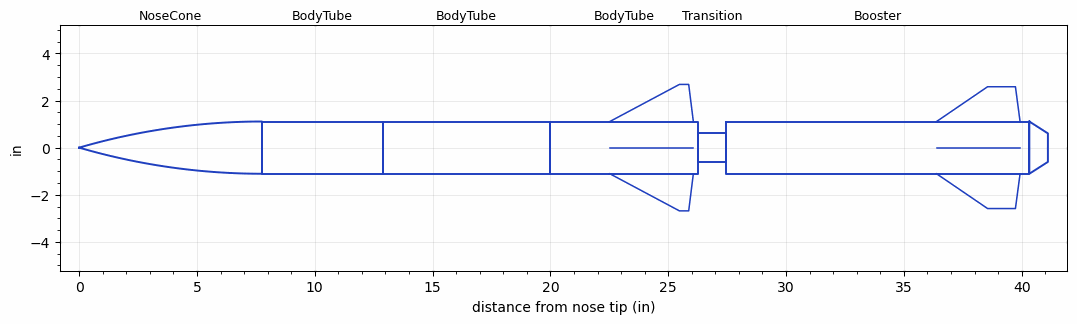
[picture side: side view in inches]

<RASAeroDocument>
 <FileVersion>2</FileVersion>
 <RocketDesign>
  <NoseCone>
   <Length>7.7579</Length>
   <Diameter>2.217</Diameter>
   <Shape>Tangent Ogive</Shape>
   <Location>0</Location>
  </NoseCone>
  <BodyTube>
   <Length>5.1181</Length>
   <Diameter>2.217</Diameter>
   <Location>7.7579</Location>
  </BodyTube>
  <BodyTube>
   <Length>7.0866</Length>
   <Diameter>2.217</Diameter>
   <Location>12.876</Location>
  </BodyTube>
  <BodyTube>
   <Length>6.2992</Length>
   <Diameter>2.217</Diameter>
   <Location>19.9626</Location>
   <Fin>
    <Count>4</Count>
    <Chord>3.5433</Chord>
    <Span>1.5748</Span>
    <SweepDistance>2.9527</SweepDistance>
    <TipChord>0.3937</TipChord>
    <Thickness>0.1181</Thickness>
    <Location>3.7401</Location>
    <AirfoilSection>Subsonic NACA</AirfoilSection>
   </Fin>
  </BodyTube>
  <Transition>
   <Length>1.1811</Length>
   <Diameter>1.2087</Diameter>
   <RearDiameter>1.2087</RearDiameter>
   <Location>26.2618</Location>
  </Transition>
  <Booster>
   <Length>12.8819</Length>
   <Diameter>2.217</Diameter>
   <RailGuideDiameter>0.3725</RailGuideDiameter>
   <RailGuideHeight>0.305</RailGuideHeight>
   <Location>27.4429</Location>
   <BoattailLength>0.7874</BoattailLength>
   <BoattailRearDiameter>1.2087</BoattailRearDiameter>
   <Fin>
    <Count>4</Count>
    <Chord>3.5433</Chord>
    <Span>1.4764</Span>
    <SweepDistance>2.1653</SweepDistance>
    <TipChord>1.1811</TipChord>
    <Thickness>0.1181</Thickness>
    <Location>3.937</Location>
    <AirfoilSection>Subsonic NACA</AirfoilSection>
   </Fin>
  </Booster>
  <Surface>Rough Camouflage Paint</Surface>
  <CD>0</CD>
  <ModifiedBarrowman>False</ModifiedBarrowman>
  <Turbulence>False</Turbulence>
  <UseBooster1>True</UseBooster1>
  <UseBooster2>False</UseBooster2>
 </RocketDesign>
 <LaunchSite>
  <Altitude>0</Altitude>
  <Pressure>29.9214</Pressure>
  <RodAngle>0</RodAngle>
  <RodLength>39.37</RodLength>
  <Temperature>59</Temperature>
  <WindSpeed>4.4739</WindSpeed>
 </LaunchSite>
 <Recovery>
  <Altitude1>656.168</Altitude1>
  <Altitude2>0</Altitude2>
  <DeviceType1>Parachute</DeviceType1>
  <DeviceType2>None</DeviceType2>
  <Event1>True</Event1>
  <Event2>False</Event2>
  <Size1>12</Size1>
  <Size2>0</Size2>
  <EventType1>Apogee</EventType1>
  <EventType2>None</EventType2>
  <CD1>0.8</CD1>
  <CD2>0</CD2>
 </Recovery>
 <SimulationList>
  <Simulation>
   <SustainerLaunchWt>1.0199</SustainerLaunchWt>
   <SustainerCG>13.2994</SustainerCG>
   <SustainerIgnitionDelay>0</SustainerIgnitionDelay>
   <Booster1LaunchWt>1.4285</Booster1LaunchWt>
   <Booster1SeparationDelay>0</Booster1SeparationDelay>
   <Booster1IgnitionDelay>0</Booster1IgnitionDelay>
   <Booster1CG>19.1534</Booster1CG>
   <IncludeBooster1>False</IncludeBooster1>
   <Booster2Delay>0</Booster2Delay>
   <IncludeBooster2>False</IncludeBooster2>
  </Simulation>
  <Simulation>
   <SustainerLaunchWt>1.0199</SustainerLaunchWt>
   <SustainerCG>13.2994</SustainerCG>
   <SustainerIgnitionDelay>0</SustainerIgnitionDelay>
   <Booster1LaunchWt>1.4285</Booster1LaunchWt>
   <Booster1SeparationDelay>0</Booster1SeparationDelay>
   <Booster1IgnitionDelay>0</Booster1IgnitionDelay>
   <Booster1CG>19.1534</Booster1CG>
   <IncludeBooster1>False</IncludeBooster1>
   <Booster2Delay>0</Booster2Delay>
   <IncludeBooster2>False</IncludeBooster2>
  </Simulation>
  <Simulation>
   <SustainerLaunchWt>1.0199</SustainerLaunchWt>
   <SustainerCG>13.2994</SustainerCG>
   <SustainerIgnitionDelay>0</SustainerIgnitionDelay>
   <Booster1LaunchWt>1.4285</Booster1LaunchWt>
   <Booster1SeparationDelay>1</Booster1SeparationDelay>
   <Booster1IgnitionDelay>0</Booster1IgnitionDelay>
   <Booster1CG>19.1534</Booster1CG>
   <IncludeBooster1>False</IncludeBooster1>
   <Booster2Delay>0</Booster2Delay>
   <IncludeBooster2>False</IncludeBooster2>
  </Simulation>
  <Simulation>
   <SustainerLaunchWt>1.0199</SustainerLaunchWt>
   <SustainerCG>13.2994</SustainerCG>
   <SustainerIgnitionDelay>0</SustainerIgnitionDelay>
   <Booster1LaunchWt>1.4285</Booster1LaunchWt>
   <Booster1SeparationDelay>2</Booster1SeparationDelay>
   <Booster1IgnitionDelay>0</Booster1IgnitionDelay>
   <Booster1CG>19.1534</Booster1CG>
   <IncludeBooster1>False</IncludeBooster1>
   <Booster2Delay>0</Booster2Delay>
   <IncludeBooster2>False</IncludeBooster2>
  </Simulation>
 </SimulationList>
</RASAeroDocument>
